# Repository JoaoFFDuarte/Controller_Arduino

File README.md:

# Controller_Arduino
This repository is for the PCB for the Controller of the Handheld Emulating Digital Console (Arduino Version)

All of the parts of the PCB were made in KiCad 8.0, an open source PCB CAD.
You can download it and learn more about it in this link: https://www.kicad.org

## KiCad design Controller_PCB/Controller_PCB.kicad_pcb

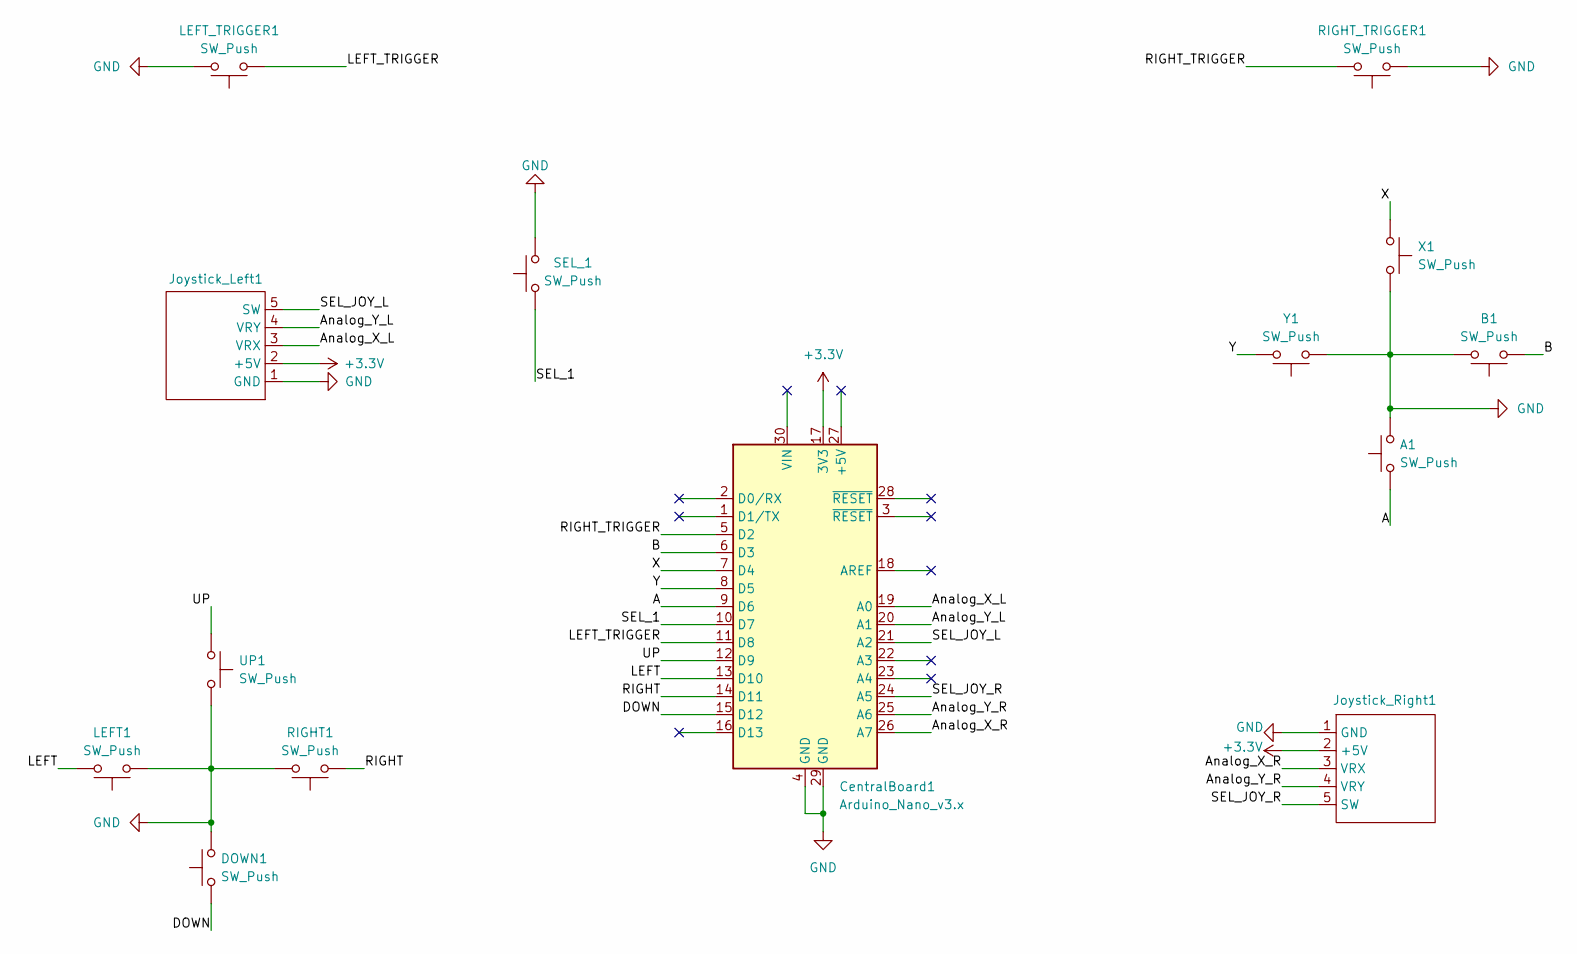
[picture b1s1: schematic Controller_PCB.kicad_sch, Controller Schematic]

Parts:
A1: SW_Push; SW_PUSH_6mm
B1: SW_Push; SW_PUSH_6mm
CentralBoard1: Arduino_Nano_v3.x; Arduino_Nano
DOWN1: SW_Push; SW_PUSH_6mm
Joystick_Left1: Joystick
Joystick_Right1: Joystick
LEFT1: SW_Push; SW_PUSH_6mm
LEFT_TRIGGER1: SW_Push; SW_PUSH_6mm
RIGHT1: SW_Push; SW_PUSH_6mm
RIGHT_TRIGGER1: SW_Push; SW_PUSH_6mm
SEL_1: SW_Push; SW_PUSH_6mm
UP1: SW_Push; SW_PUSH_6mm
X1: SW_Push; SW_PUSH_6mm
Y1: SW_Push; SW_PUSH_6mm

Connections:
+3.3V: CentralBoard1.17 (3V3), Joystick_Left1.2 (+5V), Joystick_Right1.2 (+5V)
/A: A1.1, CentralBoard1.9 (D6)
/Analog_X_L: CentralBoard1.19 (A0), Joystick_Left1.3 (VRX)
/Analog_X_R: CentralBoard1.26 (A7), Joystick_Right1.3 (VRX)
/Analog_Y_L: CentralBoard1.20 (A1), Joystick_Left1.4 (VRY)
/Analog_Y_R: CentralBoard1.25 (A6), Joystick_Right1.4 (VRY)
/B: B1.1, CentralBoard1.6 (D3)
/DOWN: CentralBoard1.15 (D12), DOWN1.1
/LEFT: CentralBoard1.13 (D10), LEFT1.2
/LEFT_TRIGGER: CentralBoard1.11 (D8), LEFT_TRIGGER1.1
/RIGHT: CentralBoard1.14 (D11), RIGHT1.1
/RIGHT_TRIGGER: CentralBoard1.5 (D2), RIGHT_TRIGGER1.2
/SEL_1: CentralBoard1.10 (D7), SEL_1.1
/SEL_JOY_L: CentralBoard1.21 (A2), Joystick_Left1.5 (SW)
/SEL_JOY_R: CentralBoard1.24 (A5), Joystick_Right1.5 (SW)
/UP: CentralBoard1.12 (D9), UP1.1
/X: CentralBoard1.7 (D4), X1.1
/Y: CentralBoard1.8 (D5), Y1.2
GND: A1.2, B1.2, CentralBoard1.4 (GND), CentralBoard1.29 (GND), DOWN1.2, Joystick_Left1.1 (GND), Joystick_Right1.1 (GND), LEFT1.1, LEFT_TRIGGER1.2, RIGHT1.2, RIGHT_TRIGGER1.1, SEL_1.2, UP1.2, X1.2, Y1.1

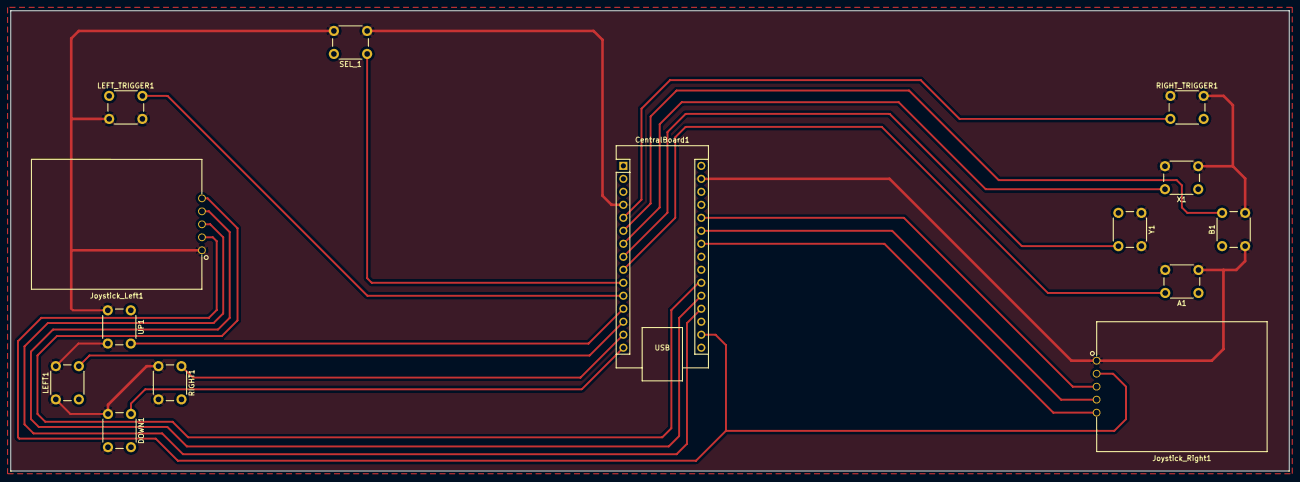
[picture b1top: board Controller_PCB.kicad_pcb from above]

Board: 2 copper layers, 250.0 x 90.0 mm, 14 parts (0 on the bottom side), 19 nets.

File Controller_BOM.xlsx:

Id | Designator | Footprint | Quantity | Designation | Price per piece | Total Price | Datasheet | Link to Parts
1 | Joystick_Left1, Joystick_Right1 | Joystick | 2 | KY-023 Joystick Module | 2.5 | 5 | https://datasheetspdf.com/pdf-down/K/Y/-/KY-023-Joy-IT.pdf | https://mauser.pt/catalog/product_info.php?products_id=096-9085
2 | RIGHT_TRIGGER1, LEFT_TRIGGER1, Y1, X1, UP1, SEL_1, RIGHT1, LEFT1, DOWN1, B1, A1 | SW_PUSH_6mm | 11 | SW_Push | 0.09 | 0.99 | https://www.cuidevices.com/product/resource/ts02.pdf | https://www.digikey.pt/pt/products/detail/cui-devices/TS02-6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
3 | CentralBoard1 | Arduino_Nano | 1 | Arduino_Nano_v3.x | 19 | 19 | https://docs.arduino.cc/resources/datasheets/ABX00083-datasheet.pdf | https://store.arduino.cc/products/nano-esp32-with-headers

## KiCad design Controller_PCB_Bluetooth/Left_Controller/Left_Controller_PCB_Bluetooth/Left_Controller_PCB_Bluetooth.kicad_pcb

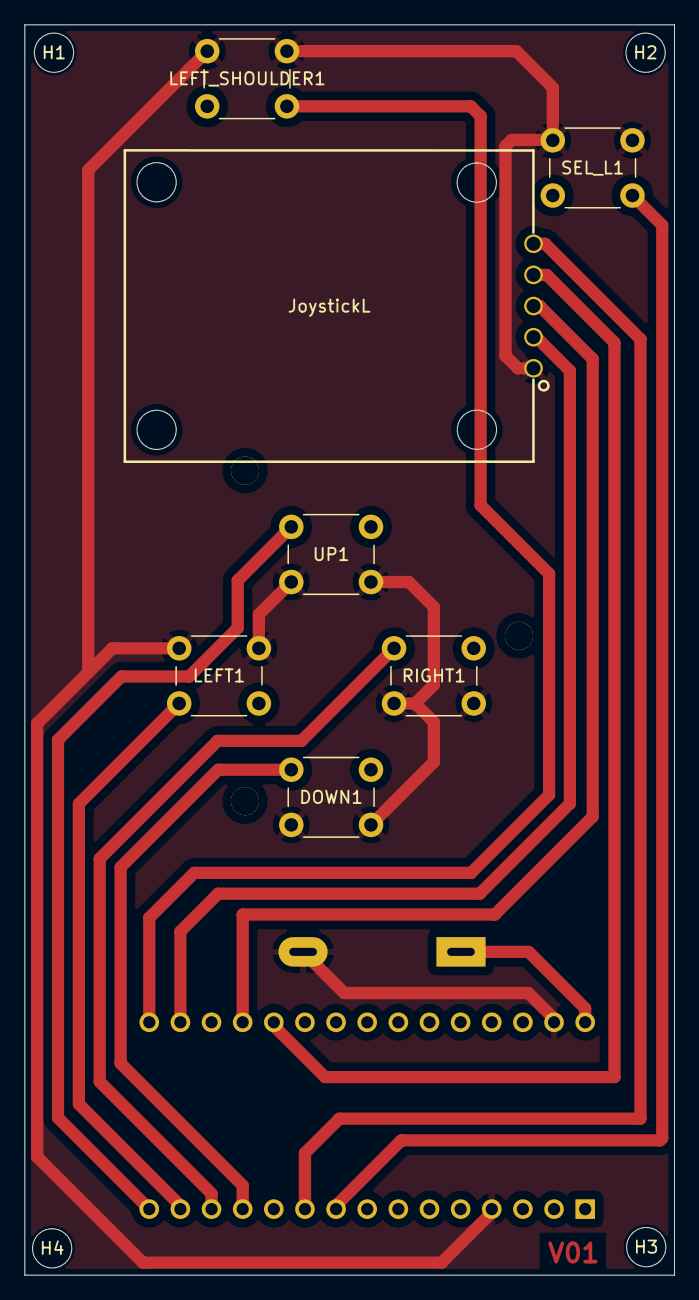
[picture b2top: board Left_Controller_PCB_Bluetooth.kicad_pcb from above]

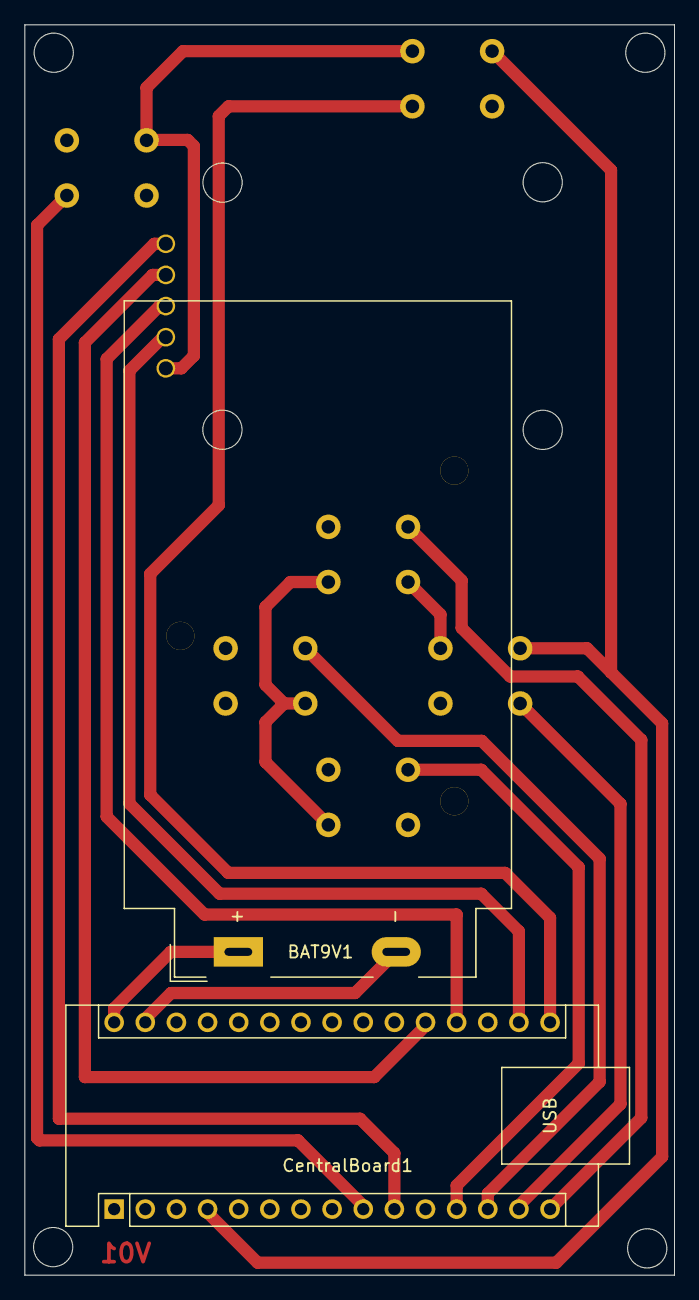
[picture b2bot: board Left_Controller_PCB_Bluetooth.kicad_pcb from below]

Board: 2 copper layers, 53.0 x 102.0 mm, 13 parts (2 on the bottom side), 12 nets.

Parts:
BAT9V1: Battery_Cell; BatteryHolder_MPD_BA9VPC_1xPP3
CentralBoard1: Arduino_Nano_v3.x; Arduino_Nano
DOWN1: SW_Push; SW_PUSH_6mm
H1, H2, H3, H4: MountingHole; MountingHole_3.2mm_M3
JoystickL1: JoystickL; Joystick
LEFT1: SW_Push; SW_PUSH_6mm
LEFT_SHOULDER1: SW_Push; SW_PUSH_6mm
RIGHT1: SW_Push; SW_PUSH_6mm
SEL_L1: SW_Push; SW_PUSH_6mm
UP1: SW_Push; SW_PUSH_6mm

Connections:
+3.3V: CentralBoard1.17 (3V3), JoystickL1.2 (+5V)
+9V: BAT9V1.1 (+), CentralBoard1.30 (VIN)
/Analog_X_L: CentralBoard1.19 (A0), JoystickL1.3 (VRX)
/Analog_Y_L: CentralBoard1.20 (A1), JoystickL1.4 (VRY)
/DOWN: CentralBoard1.12 (D9), DOWN1.1
/LEFT: CentralBoard1.14 (D11), LEFT1.2
/LEFT_SHOULDER: CentralBoard1.16 (D13), LEFT_SHOULDER1.1
/RIGHT: CentralBoard1.13 (D10), RIGHT1.1
/SEL_JOY_L: CentralBoard1.10 (D7), JoystickL1.5 (SW)
/SEL_L: CentralBoard1.9 (D6), SEL_L1.1
/UP: CentralBoard1.15 (D12), UP1.1
GND: BAT9V1.2 (-), CentralBoard1.4 (GND), CentralBoard1.29 (GND), DOWN1.2, JoystickL1.1 (GND), LEFT1.1, LEFT_SHOULDER1.2, RIGHT1.2, SEL_L1.2, UP1.2

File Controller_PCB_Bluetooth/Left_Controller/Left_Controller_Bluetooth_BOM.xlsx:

Id | Designator | Footprint | Quantity | Designation | Price per piece | Total Price | Datasheet | Link to Parts
1 | JoystickL | Joystick | 1 | KY-023 Joystick Module | 2.5 | 2.5 | https://datasheetspdf.com/pdf-down/K/Y/-/KY-023-Joy-IT.pdf | https://mauser.pt/catalog/product_info.php?products_id=096-9085
2 | LEFT_SHOULDER1, SEL_L1, UP1, , RIGHT1, LEFT1, DOWN1 | SW_PUSH_6mm | 6 | SW_Push | 0.16 | 0.96 | https://www.farnell.com/datasheets/2343587.pdf | https://mauser.pt/catalog/product_info.php?products_id=010-1107
3 | CentralBoard1 | Arduino_Nano | 1 | Arduino_Nano_v3.x | 19 | 19 | https://docs.arduino.cc/resources/datasheets/ABX00083-datasheet.pdf | https://store.arduino.cc/products/nano-esp32-with-headers
4 | BAT9V1 | BatteryHolder_MPD_BA9VPC_1xPP3 | 1 | Battery Holder 9V | 0.62 | 0.62 | -------------------------------------------------------------------- | https://www.ptrobotics.com/suporte-pilhas/5015-battery-holde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

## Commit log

2024-04-02 Added KiCad Files to the project
    This is revision V01
2024-04-02 Added KiCad files
    This is revision V01
2024-04-02 Uploaded KiCad Files
    This is revision V01 (for real this time, the version labels are now right)
2024-04-02 Added KiCad Files
    This is revision V01 (for real this time, the version labels are now right)
2024-05-07 Added Left Controller for Bluetooth Controllers
2024-05-08 Added Right Controller and updated Left one
    Added the Right Controller!
    There was also an error in the Left Controller Gerber files where the Back Silkscreen wasn't plotted.
